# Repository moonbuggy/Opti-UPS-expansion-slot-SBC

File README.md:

# Opti-UPS Expansion Slot Single Board Computer

KiCad files for circuits built on prototyping board that will fit in a UPS
expansion slot, to add an ethernet interface for network UPS management.

*   [Rationale](#rationale)
*   [Single Board Computers](#single-board-computers)
*   [Expansion Boards](#expansion-boards)
    +   [Assembled](#assembled)
    +   [Schematics](#schematics)
    +   [Layouts](#layouts)
    +   [Components](#components)
        -   [Pre-built Modules](#pre-built-modules)
        -   [Mounting](#mounting)
    +   [Status LED](#status-led)
    +   [I²C Header](#i-c-header)
        -   [Real-time Clock](#real-time-clock)
    +   [Fan Connector](#fan-connector)
    +   [Power Cycling](#power-cycling)
*   [Opti-UPS PS1440RM](#opti-ups-ps1440rm)
    +   [Expansion Slot](#expansion-slot)
    +   [Pinouts](#pinouts)
*   [Software](#software)
    +   [NUT](#nut)
        -   [Minimal configuration](#minimal-configuration)
    +   [chrony](#chrony)
    +   [Windows 2000 in Docker](#windows-2000-in-docker)
        -   [/etc/docker/daemon.json](#-etc-docker-daemonjson)
        -   [Dockerfile](#dockerfile)
        -   [docker-compose.yml](#docker-composeyml)
*   [Links](#links)
    +   [Datasheets](#datasheets)

These are designed with an Opti-UPS PS1440RM in mind, but should work in other
UPS expansion slots after adjusting for the pinout of the expansion slot
connection.

There's two different boards, for two different SBCs: an
[Orange Pi Zero](http://www.orangepi.org/orangepiwiki/index.php/Orange_Pi_Zero)
and a [Rock Pi S](https://wiki.radxa.com/RockpiS). There's more information here
about the Rock Pi S version because that's the one I ended up building.

## Rationale
My UPS is 20 years old but still works fine. Except, the official Opti-UPS
software for the UPS won't run in anything newer than Windows 2000 and I don't
want to run a VM on a real computer just to talk to the UPS.

Also, it's just nice to have ethernet coming right out of a UPS, rather than a
serial cable.

Proper expansion cards for the UPS aren't easy to find, due to its age, so
making something to fit seems sensible.

## Single Board Computers
The two SBCs offer different solutions to the problem. The Orange Pi Zero is
cheap and will happily run [Network UPS Tool (NUT)](https://networkupstools.org/).
The Rock Pi S is also relatively cheap, but _should_ be able to run [Windows 2000
in Docker](https://github.com/hectorm/docker-qemu-win2000), allowing the official
Opti-UPS software to run.

The Rock Pi S will want to draw more power than the Orange Pi Zero, and it's
overkill for just running NUT (which it will also happily do), but it is more
capable thus provides more flexibility.

These boards will work directly with other SBCs that have the same pin
arrangement (e.g. Orange Pi Zero 2 and Orange Pi Zero 3), although the spaces
in the boards to fit RJ-45/USB sockets and any CPU heatsinks may need to be
adjusted.

It's not too difficult to customise these boards for other SBCs with different
pin arrangements.

## Expansion Boards
Both boards are fundamentally the same. The main differences are the physical
layout of headers on the SBC they connect to, and the function of each header
pin. It's just a matter of routing tracks appropriately.

The Rock Pi S board does have a [power cycling circuit](#power-cycling) that the
Orange Pi Zero board lacks.

The UPS is connected to _UART2_ (_/dev/ttyS2_) on the Orange Pi Zero and _UART3_
(_/dev/ttyS3_) on the Rock Pi S. There's an overlay in `root/boot/overlay-user/`
to enable the UART on the Rock Pi S.

### Assembled
<p><br/>
<em>Rock Pi S board (top)</em></p>

<p><br/>
<em>Rock Pi S board (side)</em></p>

### Schematics
<p><br/>
<em>Orange Pi Zero schematic</em></p>

<p><br/>
<em>Rock Pi S schematic</em></p>

### Layouts
<p><br/>
<em>Orange Pi Zero layout</em></p>

<p><br/>
<em>Rock Pi S layout</em></p>

The scales around the boards are indicating the number of holes in the PCB,
with a 2.54mm pitch. Thus each increment is equal to 2.54mm.

In most cases, blue tracks should be copper on the bottom of the PCB and red
tracks should be wires on top of the PCB. The thin blue tracks running between
pads on the pin headers will need to be insulated wire.

There's a whole bunch of ground tracks on both PCBs, particularly around the
RS-232 and TTL serial signals, in an attempt to minimise noise in these signals
by guarding their tracks.

The test points on the Rock Pi S board are for convenient diagnostics of the
serial link and the fan's PWM and tachometer signals. They can be omitted.

The modules all have multiple common ground pins, and the MAX3232 module has
multiple common supply pins as well. Any tracks in the layout under/over these
modules connecting these common pins are pre-existing on the modules and don't
need to be created on the PCB.

### Components
#### Pre-built Modules
The power supply and RS-232<->TTL converters on these boards are pre-built
modules, soldered directly to the main board. Suitable modules are cheap on
eBay/AliExpress or from other sources, and they make routing conductors on
prototype board a lot simpler.

There should be room to fit modules of different dimensions than those I've used
without needing to move anything but some conductors. If desired, extending
the length of the board provides ample room to build these modules from scratch
on the board itself.

##### Switching Power Supply - MP4560
<p><br/>
<em>MP4560 module</em></p>

We'll be sourcing 12V DC from the UPS expansion slot's connector and regulating
down to 5V for the SBC. An efficient switching supply makes a lot more sense
than a linear regulator, both in terms of heat generation and the current we'll
want to pull through a 28AWG ribbon cable.

The MP4560 seems a good choice because the high switching frequency means the
inductor can be physically smaller than slower options (e.g. LM2596), so there's
not going to be any issue with clearance for a toroid inside the expansion slot.
High switching frequencies should result in less ripple in the output as well.

The module performs well in a load test and shouldn't have any problems meeting
the power demands of the SBCs.
<p><br/>
<em>MP4560 module load test</em></p>

##### RS-232 <-> TTL Converter - MAX3232/SP3232
<p><br/>
<em>MAX3232 module</em></p>

<p><br/>
<em>SP3232 module</em></p>

The UPS is providing real zero-crossing RS-232, which doesn't do an SBC GPIO any
good, so we need to convert this to the 0-3.3V TTL level the SBC expects. The
MAX3232 seems a good option to do this, however the cheap chips are often
counterfeit and can have issues with noise or lifespan as a result. It could be
worth trying a module using the equivalent SP3232 chip, it may increase the odds
of getting a real chip.

This module sources its 3.3V supply from the SBC's GPIO, so we don't need
another standalone switching supply.

#### Mounting
Right-angled M3 screw terminals are used for mounting the board on the blanking
panel that covers the expansion bay, after cutting appropriate holes for the
RJ-45 socket and the USB port.

<p><br/>
<em>Right-angle M3 screw terminal</em></p>

### Status LED
The status LED will be red when the SBC is powered but can be changed to green
via the GPIO. Switching this LED to green when relevant software is loaded
means we have an indication for both 'powered' and 'ready'.

The Orange Pi Zero board uses the 5V supply for the LEDs, and the Rock Pi S
uses the 3.3V supply. This is entirely due to the physical proximity of a supply
rail in each case.

To control the green LED, the Orange Pi Zero board uses pin 118/PA19 (chip 0,
offset 19) and the Rock Pi S boards uses pin 46/GPIO2_A6 (chip 2, offset 6).

If using NUT, the simplest method of control is to create a systemd unit file
for the LED which starts and stops with the _nut_ target. For example,
on the Rock Pi S (note the arguments to _gpioset_ in ExecStart/ExecStop):

##### /etc/systemd/system/ready-led.service
```ini
[Unit]
Description='ready' status indicator LED
After=nut-server.service nut-driver.target
Requires=nut-server.service nut-driver.target
PartOf=nut.target

[Service]
Type=oneshot
ExecStart=gpioset 2 6=1
ExecStop=gpioset 2 6=0
RemainAfterExit=yes

[Install]
WantedBy=nut.target
```

To enable the service:
```sh
sudo systemctl daemon-reload
sudo systemctl enable ready-led
```

Things are a bit more complicated if running Windows 2000 (or NUT) in Docker,
which isn't yet documented here.

To disable the SBC's onboard LEDs (which won't be visible once the board is
installed in the UPS) apply the
[rock-pi-s-disable-leds.dts](root/boot/overlay-user/rock-pi-s-disable-leds.dts)
overlay.

### I²C Header
An I²C connection is made available through jumper pins. This can be used for
any I²C device, but a UPS could be a good place for a real time clock and NTP
server.

#### Real-time Clock
There are many options available, but the easiest is to buy a cheap pre-built
module. The pin header has an appropriate layout for some modules to plug
directly in. For example:

<p><br/>
<em>DS3231 RTC module</em></p>

The _i2c1_ bus on the Rock Pi S can be enabled with the
[rock-pi-s-i2c1.dts](root/boot/overlay-user/rock-pi-s-i2c1.dts) overlay, and
there's an overlay for a [DS3231N RTC](root/boot/overlay-user/rtc-ds3231n.dts)
as well.

### Fan Connector
The 4-wire fan connector provides the option to power and control a 12V fan from
this board.

For a while the fan in my UPS wasn't spinning. It turned out I'd not attached it
to the right connector in the UPS, but I'd already added the fan connector to
this board, so here it is.

Both the tachometer and RPM signals are 3.3V.

The pull-up resistor on the tachometer signal may not be necessary if we set an
internal pull-up on the SBC, but there's no real harm in doing it in hardware
instead of software.

A 2-wire or 3-wire fan, without a PWM input, can be driven by the MOSFET, if the
nearby jumper is open. If using a 4-wire fan the jumper should be closed,
disabling the MOSFET and letting the PWM signal drive the fan directly.

The IRLZ44N MOSFET is overkill for a fan, but it's easily available and
relatively cheap. Depending on the fan and the duty cycle, a BS170 or something
similar in a TO-92 package could work. An SMD MOSFET, like the SSM3K102TU used
elsewhere on the Rock Pi S board, would also work.

### Power Cycling
The Rock Pi S board will disconnect the SBC from the power when two conditions
are both met:

1.  the UPS signals a loss of mains power by pulling pin 4 on the ribbon cable
    to ground
1.  the SBC signals it has shut down by switching pin 22//GPIO2_A7 (chip 2,
    offset 7) from 3.3V to high impedance

Power will be restored automatically once the UPS indicates mains is restored by
switching ribbon cable pin 4 open circuit, which should in turn cause the SBC to
boot.

The capacitor on the SBC's GPIO signal provides a delay before cutting power
(47uF should be around 30 seconds through the 1M resistor) to ensure ample time
is provided, as the GPIO pin will be pulled low at some midpoint in the shutdown
process rather than at the very end.

We can start a systemd service to indicate we're booting very early in the init
process as such:

##### /etc/systemd/system/booting-signal.service
```ini
[Unit]
Description=boot indication
After=local-fs.target
Requires=local-fs.target
Before=sysinit.target
DefaultDependencies=false

[Service]
Type=oneshot
ExecStart=gpioset -D open-source 2 7=1
ExecStop=gpioset -D open-source 2 7=0
RemainAfterExit=yes

[Install]
WantedBy=sysinit.target
```

To enable the service:
```sh
sudo systemctl daemon-reload
sudo systemctl enable booting-signal
```

The `-D open-source` argument to `gpioset` ensures we don't discharge the
time delay capacitor into the GPIO. Using the default `-D push-pull`
configuration would result in the time delay reducing to less than a second,
effectively disabling the delay in practice.

The push button emulates a loss of mains signals from the UPS and allows us to
cycle the power and restart the SBC if it's been shutdown manually or by some
method that didn't involve a loss of mains power. The button does nothing if the
SBC is signalling it's booted/booting.

## Opti-UPS PS1440RM
### Expansion Slot
The expansion slot has a PCB edge connector in it, connected to a 2x13 pin
socket on the UPS main board via a ribbon cable.

Instead of making a board precise enough to fit into this edge connector, it's
simpler to swap the ribbon cable for one with 2x13 pin connectors on each end,
feed one end through the hole in the expansion slot housing that held the
edge connector, and connect directly to the board.

### Pinouts
The DB9 connector on the UPS is not wired for standard RS-232:
<p><br/>
<em>Opti-UPS PS1440RM DB9 connector pinout</em></p>

The cable that comes with the UPS switches wires around so that the other end
of it is wired in the standard way for RS-232. There appear to be diodes present
as well.

Some of the pins in the expansion slot connector are common with those in the
DB9 connector, so we have an easy way to find the data pins in the expansion
slot.

Probing the 2x13 header with a multimeter and component tester (via a long
ribbon cable, so as not to work inside a live UPS) makes the 12V DC supply pins
apparent.

<p><br/>
<em>PS1440RM cable and header pinouts</em></p>

## Software
### NUT
It may be necessary to manually add the _nut_ user to the _dialout_ and/or _tty_
groups, so it has permissions for the serial device:

```sh
sudo usermod -a -G dialout nut
sudo usermod -a -G tty nut
```

The _uart3_ interface on the Rock Pi S can be enabled with the
[rock-pi-s-uart3.dts](root/boot/overlay-user/rock-pi-s-uart3.dts) overlay.

#### Minimal configuration
##### /etc/nut/ups.conf
```ini
[ps1440rm]
  driver = optiups
  port = /dev/ttyS3
  desc = "Opti-UPS PS-1440RM"
```

##### /etc/nut/upsd.conf
```sh
# listen to all IPv4
LISTEN 0.0.0.0 3493
```

#### /etc/nut/nut.conf
```conf
# enable remote connections
MODE=standalone
```

##### /etc/nut/upsd.users
```sh
[upsmon]
  password = password
  upsmon primary
```

##### /etc/nut/upsmon.conf
Setting `powervalue` to zero means we're just monitoring, this device won't be
shut down when power fails. `MINSUPPLIES` needs to be zero to allow this.

```sh
MONITOR ps1440rm@localhost 0 upsmon password primary
MINSUPPLIES 0
```

This configuration is not suitable for production.

It's important to shut the SBC down once battery levels are low, because we
don't know whether the UPS will cut the 12V supply we're using to protect the
batteries from over-discharge. In the case of the Rock Pi S board, the SBC will
automatically start again once mains power is restored. See
[Power Cycling](#power-cycling).

##### /etc/systemd/system/nut-server.service.d/override.conf
```ini
[Unit]
# Sometimes nut-server can fail to start at boot due to the network not being up
Wants=nut-driver.target network-online.target
Requires=network.target network-online.target
```

### chrony
The default configuration for the RTC is for chrony to tell the system to set it
every 11 minutes. To let chrony set the time from the RTC (as a backup if
there's some issue with the GPS), it needs to be run with the -s argument.

##### /etc/default/chrony
```sh
# This is a configuration file for /etc/init.d/chrony and
# /lib/systemd/system/chrony.service; it allows you to pass various options to
# the chrony daemon without editing the init script or service file.

# Options to pass to chrony.
DAEMON_OPTS="-F 1 -r -m -s"
```

### Windows 2000 in Docker
> [!NOTE]
> This is still a work in progress and is not complete. The official software
> doesn't necessarily offer any advantage over running NUT and this may be a waste
> of time and effort.
>
> The Docker container runs okay, but is somewhat sluggish. The Opti-UPS software
> installs and runs. However, as it stands at the moment, the COM port isn't
> functioning inside Windows 2000. This presents as a driver issue, but I assume
> the root cause is me misunderstanding the QEMU configuration,.

We can start with the [hectorm/qemu-win2000](https://hub.docker.com/r/hectorm/qemu-win2000)
Docker image and install the official Opti-UPS software to monitor things.

This will require an SD card installed into the Rock Pi S, as there's not enough
room on the 4GB eMMC for the OS and the image. To move the Docker data files to
the SD card (after it has been formatted and mounted):

#### /etc/docker/daemon.json
```json
{
        "data-root": "/mnt/sdcard/docker/"
}
```

The image requires _qemu-kvm_:
```sh
sudo apt-get install --no-install-recommends qemu-kvm
```

#### Dockerfile
It looks like we need to modify the image to tell QEMU the serial port exists.
We're using UART3 which will be _/dev/ttyS3_ in Armbian and made available as
the same in the Docker container.

QEMU, running inside the container, can be pointed in the right direction as
such:
```Dockerfile
FROM "hectorm/qemu-win2000:latest-arm64v8"

ENV VM_SERIAL_DEVICE="ttyS3"

RUN awk '!f && sub(/if/, "set -- \"$@\" -chardev serial,path=\"/dev/${VM_SERIAL_DEVICE:-ttyS3}\",id=hostserial\nset -- \"$@\" -device pci-serial,chardev=hostserial\n\nif"){f=1} 1' \
        /etc/runit/runsvdir/default/qemu/run > ./run.temp \
  && cat ./run.temp > /etc/runit/runsvdir/default/qemu/run \
  && rm -f ./run.temp
```

Build with: `docker build -t moonbuggy2000/qemu-win2000-opti-ups:latest-arm64v8 .`

> [!WARNING]
> This doesn't work. The port appears but Windows 2000 doesn't find suitable
> drivers for it. Using `isa-serial` instead of `pci-serial` leads to the driver
> installing automatically and apparently without complaint, but it doesn't seem
> to be getting data from the UPS in that case either.

#### docker-compose.yml
We don't have a huge amount of RAM to play with, and things slow to a crawl if
we're heavily using the zram, so we'll need to limit the RAM the container can
use.

```yaml
version: '3.9'

services:
  opti-ups:
    image: moonbuggy2000/qemu-win2000-opti-ups:latest-arm64v8
    container_name: opti-ups
    hostname: opti-ups
    restart: unless-stopped
    ports:
      - 3389:3389/tcp
      - 5900:5900/tcp
      - 6080:6080/tcp
    devices:
      - "/dev/kvm:/dev/kvm"
      - "/dev/ttyS3:/dev/ttyS3"
    environment:
      - "VM_CPU=3"
      - "VM_KVM=1"
      - "VM_RAM=128M"
      - "VM_SERIAL_DEVICE=ttyS3"
    volumes:
      - "opti-ups:/mnt"
    network_mode: bridge

volumes:
  opti-ups:
    driver: local
    name: opti-ups
```

## Links
### Datasheets
*   [BS170](https://www.onsemi.com/pdf/datasheet/mmbf170-d.pdf)
*   [DS3231](https://www.analog.com/media/en/technical-documentation/data-sheets/DS3231.pdf)
*   [IRLZ44N](https://www.infineon.com/dgdl/Infineon-IRLZ44N-DataSheet-v01_01-EN.pdf?fileId=5546d462533600a40153567217c32725)
*   [MAX3232](https://www.analog.com/media/en/technical-documentation/data-sheets/MAX3222-MAX3241.pdf)
*   [MP4560](https://www.monolithicpower.com/en/documentview/productdocument/index/version/2/document_type/Datasheet/lang/en/sku/MP4560/document_id/305)
*   [SP3232](https://assets.maxlinear.com/web/documents/sipex/datasheets/sp3222e_sp3232e.pdf)
*   [SSM3K102TU](https://au.mouser.com/datasheet/2/408/21598-27399.pdf)

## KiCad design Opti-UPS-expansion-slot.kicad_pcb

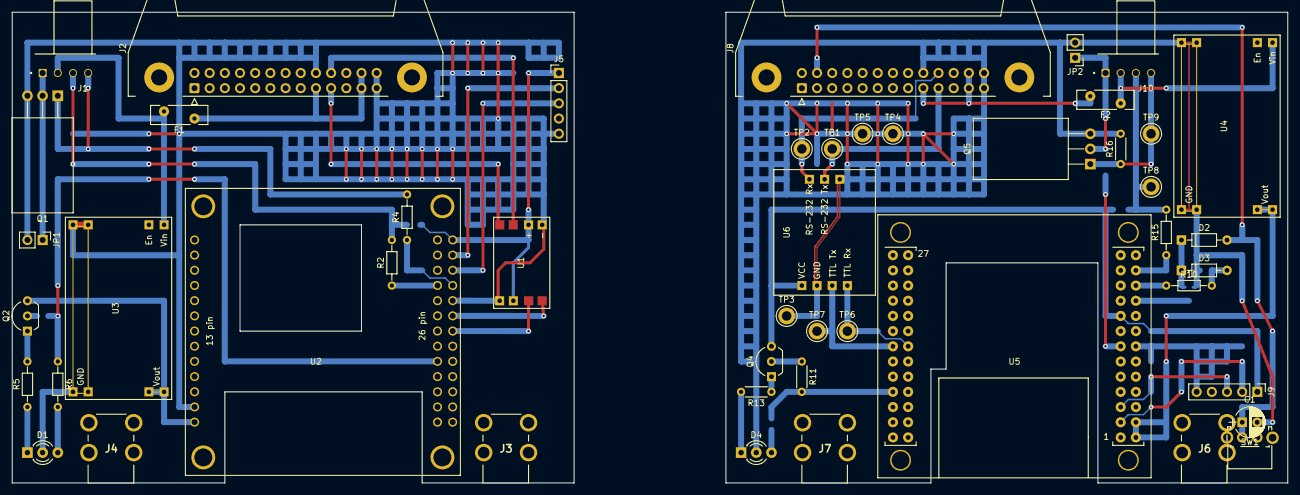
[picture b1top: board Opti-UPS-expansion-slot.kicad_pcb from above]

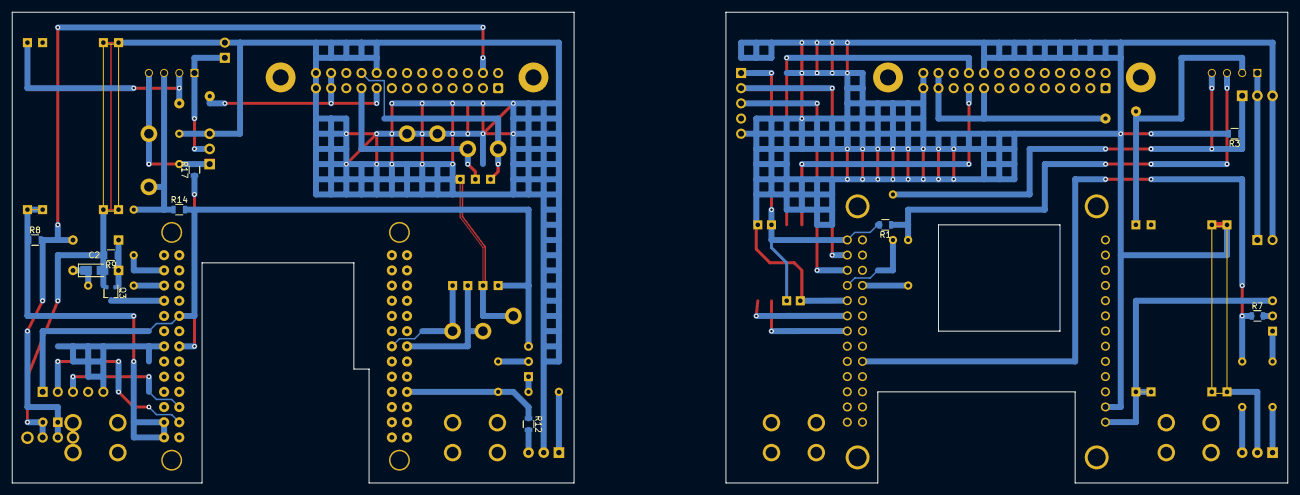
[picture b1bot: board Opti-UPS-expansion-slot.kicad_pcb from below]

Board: 2 copper layers, 213.4 x 78.7 mm, 58 parts (10 on the bottom side), 46 nets.

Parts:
C1: 1uF; CP_Radial_D5.0mm_P2.50mm
C2: 47uF; CP_Tantalum_Case-A_EIA-3216-18_Reflow
D1, D4: LED_Dual_ACA; LED_D3.0mm-3
D2, D3: BAT43; D_DO-35_SOD27_P7.62mm_Horizontal
F1: 0.5-1A; Fuse_Bourns_MF-RHT200
F2: 1-2A; Fuse_Bourns_MF-RHT200
J1, J10: PWM Fan; Fan_Pin_Header_4Pin_Horizontal
J2, J8: Expansion_Slot_Ribbon_Connector; IDC-Header_2x13-1MP_P2.54mm_Latch_Horizontal
J3, J4, J6, J7: M3-Screw-Terminal-90
J5, J9: I2C Header; Pin_Header_Straight_1x05_Pitch2.54mm
JP1, JP2: Jumper_2_Open; Pin_Header_Straight_1x02_Pitch2.54mm
Q1: IRFZ44N; TO-220-3_Horizontal
Q2, Q4: BC557; TO-92_Inline_Wide
Q3: SM3K102TU; SOT-323_SC-70
Q5: IRLZ44N; TO-220-3_Horizontal
R1, R14: 2k2; R_0805
R2, R4: 50; R_Axial_DIN0204_L3.6mm_D1.6mm_P7.62mm_Horizontal
R3: 10k; R_0805
R5, R6, R10: 1k5; R_Axial_DIN0204_L3.6mm_D1.6mm_P7.62mm_Horizontal
R7, R8: 15k; R_0805
R9: 1M; R_0805
R11: 15k; R_Axial_DIN0204_L3.6mm_D1.6mm_P5.08mm_Horizontal
R12: 1k5; R_0805
R13: 8k2; R_Axial_DIN0204_L3.6mm_D1.6mm_P5.08mm_Horizontal
R15: 47; R_Axial_DIN0204_L3.6mm_D1.6mm_P7.62mm_Horizontal
R16: 10k; R_Axial_DIN0204_L3.6mm_D1.6mm_P5.08mm_Horizontal
R17: 47; R_0805
SW1: SW_Push; SW_Tactile_SPST_Angled_PTS645Vx83-2LFS
TP1, TP7: TestPoint; Test_Point_Keystone_Yellow
TP2, TP6: TestPoint; Test_Point_Keystone_Green
TP3, TP4, TP5: TestPoint; Test_Point_Keystone_Black
TP8: TestPoint; Test_Point_Keystone_White
TP9: TestPoint; Test_Point_Keystone_Blue
U1: MAX3232_Module
U2: orange_pi_zero; orangepi-zero-headers-no-debug
U3, U4: MP4560_Regulator_Module
U5: RockPi-S; RockPi-S-pads-only
U6: SP3232_Module; SP3232_Module_1CH

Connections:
+3V3: J9.1, Q4.3, R14.2, U5.17, U6.1
+12V: F1.1, F2.2, J2.17, J2.23, J2.24, J8.17, J8.23, J8.24
/Orange Pi Zero/GPIO_ready: R6.1, R7.1, U2.118
/Orange Pi Zero/PWM: J1.4, Q1.1, R3.1, R4.2
/Orange Pi Zero/RS232-Rx: J2.19, U1.8
/Orange Pi Zero/RS232-Tx: J2.20, U1.7
/Orange Pi Zero/SCL: J5.3, U2.105
/Orange Pi Zero/SDA: J5.2, U2.103
/Orange Pi Zero/TTL-Rx: U1.4, U2.111
/Orange Pi Zero/TTL-Tx: U1.3, U2.113
/Orange Pi Zero/green: D1.3, R6.2
/Orange Pi Zero/red: D1.1, R5.1
/Orange Pi Zero/tacho: J1.3, R1.1, R2.2
/Rock Pi S/FAN_GND: J10.1, JP2.1, Q5.2
/Rock Pi S/GPIO_ready: R11.2, R12.1, U5.46
/Rock Pi S/PWM: J10.4, Q5.1, R16.1, R17.2, TP9.1
/Rock Pi S/RS232-Rx: J8.19, TP1.1, U6.6
/Rock Pi S/RS232-Tx: J8.20, TP2.1, U6.7
/Rock Pi S/SCL: J9.3, U5.5
/Rock Pi S/SDA: J9.2, U5.3
/Rock Pi S/green: D4.3, R12.2
/Rock Pi S/red: D4.1, R13.2
/Rock Pi S/tacho: J10.3, R14.1, R15.2, TP8.1
GND: C1.2, C2.2, D1.2, D4.2, J2.18, J2.25, J2.26, J5.5, J8.18, J8.25, J8.26, JP1.2, JP2.2, Q1.3, Q3.2, Q5.3, R3.2, R9.2, R16.2, SW1.1, TP3.1, TP4.1, TP5.1, U1.1, U1.5, U2.2, U2.109, U3.3, U3.4, U3.5, U3.6, U4.3, U4.4, U4.5, U4.6, U6.2, U6.5
unnamed: C1.1, D2.2, J8.4, R8.2, SW1.2
unnamed: C2.1, D3.2, R10.2
unnamed: D2.1, D3.1, Q3.1, R9.1
unnamed: J1.1, JP1.1, Q1.2
unnamed: Q2.1, R5.2
unnamed: Q2.2, R7.2
unnamed: Q3.3, U5.20
unnamed: Q4.1, R13.1
unnamed: Q4.2, R11.1
unnamed: R10.1, U5.22
OPiZ-3V3: J5.1, R1.2, U1.2, U1.6, U2.101
OPiZ-5V: Q2.3, U2.1, U3.7, U3.8
OPiZ-12V-fused: F1.2, J1.2, U3.1
OPiZ-Fan-PWM: R4.1, U2.107
OPiZ-Fan-Tacho: R2.1, U2.108
RPiS-5V: R8.1, U4.7, U4.8, U5.2, U5.4
RPiS-12V-fused: F2.1, J10.2, U4.1
RPiS-Fan-PWM: R17.1, U5.13
RPiS-Fan-Tacho: R15.1, U5.24
RPiS-I2C-GND: J9.5, U5.14
RPiS-TTL-Rx: TP7.1, U5.40, U6.3
RPiS-TTL-Tx: TP6.1, U5.39, U6.4

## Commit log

2024-01-05 revision 1.1
2024-02-29 reorganized files/ -> root/
